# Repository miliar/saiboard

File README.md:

# Saiboard
Saiboard is an open-source Go board that combines tradition with technology.

Experience the thrill of Go on a real board, enhanced by AI guidance and analysis tools.

Play against AI, review your games with AI assistance, and elevate your Go skills to new heights.

https://github.com/miliar/saiboard/assets/35922697/eb32aec5-f142-464d-a071-56e9dbfe0f72

Features:

- Wooden Go [board](https://github.com/miliar/saiboard/tree/main/board) for authentic gameplay
- Sensory [electronics](https://github.com/miliar/saiboard/tree/main/electronics) for accurate move detection and LED feedback
- Heavy, magnetic Go [stones](https://github.com/miliar/saiboard/tree/main/stones) for a stable and engaging experience
- [Software](https://github.com/miliar/saiboard/tree/main/software ) with integrated AI system KataGo for expert insights and game recommendations
- User-friendly [web app](https://github.com/miliar/saiboard/tree/main/software/flutter/saiboard) for effortless control and interaction

## App

## Board
### Next moves

### Top moves

### Ownership

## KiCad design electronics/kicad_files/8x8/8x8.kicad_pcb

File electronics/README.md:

# Electronics
The electronics consists of one touch plate, an array of 19x19 hall sensors (for detecting magnets) and LEDs. \
The touch plate is used to detect when a move is finished, so that sliding the stone in position is possible. \
It is controlled by an ESP32S3 microcontroller.\
To make the manufacturing process easier, the board is divided into several smaller PCBs. \
There is a power connection for a raspberry pi.

## How to build
### PCBs

- [Order](https://jlcpcb.com/) PCB/ Stencil
- [Solderpaste](https://www.mouser.de/ProductDetail/Chip-Quik/TS391AX50?qs=1mbolxNpo8c66lK8U%252Bbg8g%3D%3D)
- Solder led side first
- [Reflow oven](https://www.ninjakitchen.de/produkte/ninja-foodi-8-in-1-multifunktionsofen-sp101eu-zidSP101EU?gclid=CjwKCAiAg6yRBhBNEiwAeVyL0K_J3ElNVxI_Z_oyhJKBGCfaiXaV0-DiEXvF-BnwtabYrZho8xsRyhoCo1UQAvD_BwE): Bake 3 min, 0-90s: 125° C, 90-180s: 230° C, then open door

- Print [plastic parts](/electronics/3d_prints/)
- Place pcb mask on first side, apply paste to the second side. Then remove pcb mask and bake pcb while placed on e.g. nuts

### Touch plate
Put copper foil on printed pcb-masks, remove foil from holes. Eletrical and physical connect all pcb masks. Glue non copper side to pcb first side with double sided tape. Solder connection to copper side and connect to touch pin of microcontroller.

### Mounting
- Press [esp32s3](https://docs.espressif.com/projects/esp-idf/en/latest/esp32s3/hw-reference/esp32s3/user-guide-devkitc-1.html#getting-started) in socket
- Use [screws](https://www.amazon.de/gp/product/B00XPJG1OC/ref=ppx_yo_dt_b_asin_title_o05_s00?ie=UTF8&psc=1) out of **stainless steel**.
- Enlarge mount holes of raspberry pi 4 to 3mm and fix it with the plastic mount. Connect power pins to board.
- Connect board power out to [adapter](https://www.amazon.de/Delock-Terminalblock-2pin-5mm-65421/dp/B009PH1J5Y/ref=pe_27091401_487027711_rtpb_2/259-0379054-1449235/ref=rtpb?_encoding=UTF8&pd_rd_i=B009PH1J5Y&pd_rd_w=x8W3O&content-id=amzn1.sym.474647f1-64c1-44ba-87f5-6213cf212586&pf_rd_p=474647f1-64c1-44ba-87f5-6213cf212586&pf_rd_r=0J4VFHEDP0EWMRD7EHXF&pd_rd_wg=oGq6l&pd_rd_r=6c2ec190-8354-4455-b1a1-8aa1fa129738&th=1). Glue adapter into hole on the side of the board.
- Use a 5V/ 10A, 50W [power supply](https://www.amazon.de/LEICKE-Netzteil-Adapter-WS2812B-LED8806/dp/B07YVBHH6K?pd_rd_w=0m35S&content-id=amzn1.sym.5a3fbeeb-1af1-4617-a0f9-8268dbe71de3&pf_rd_p=5a3fbeeb-1af1-4617-a0f9-8268dbe71de3&pf_rd_r=37PZ5YX5WHR4K52V4X9C&pd_rd_wg=4ZrhK&pd_rd_r=1ae78b2e-2f51-4e24-866a-adc47f1cd7c7&pd_rd_i=B07YVBHH6K&psc=1&ref_=pd_basp_d_rpt_ba_s_3_t)

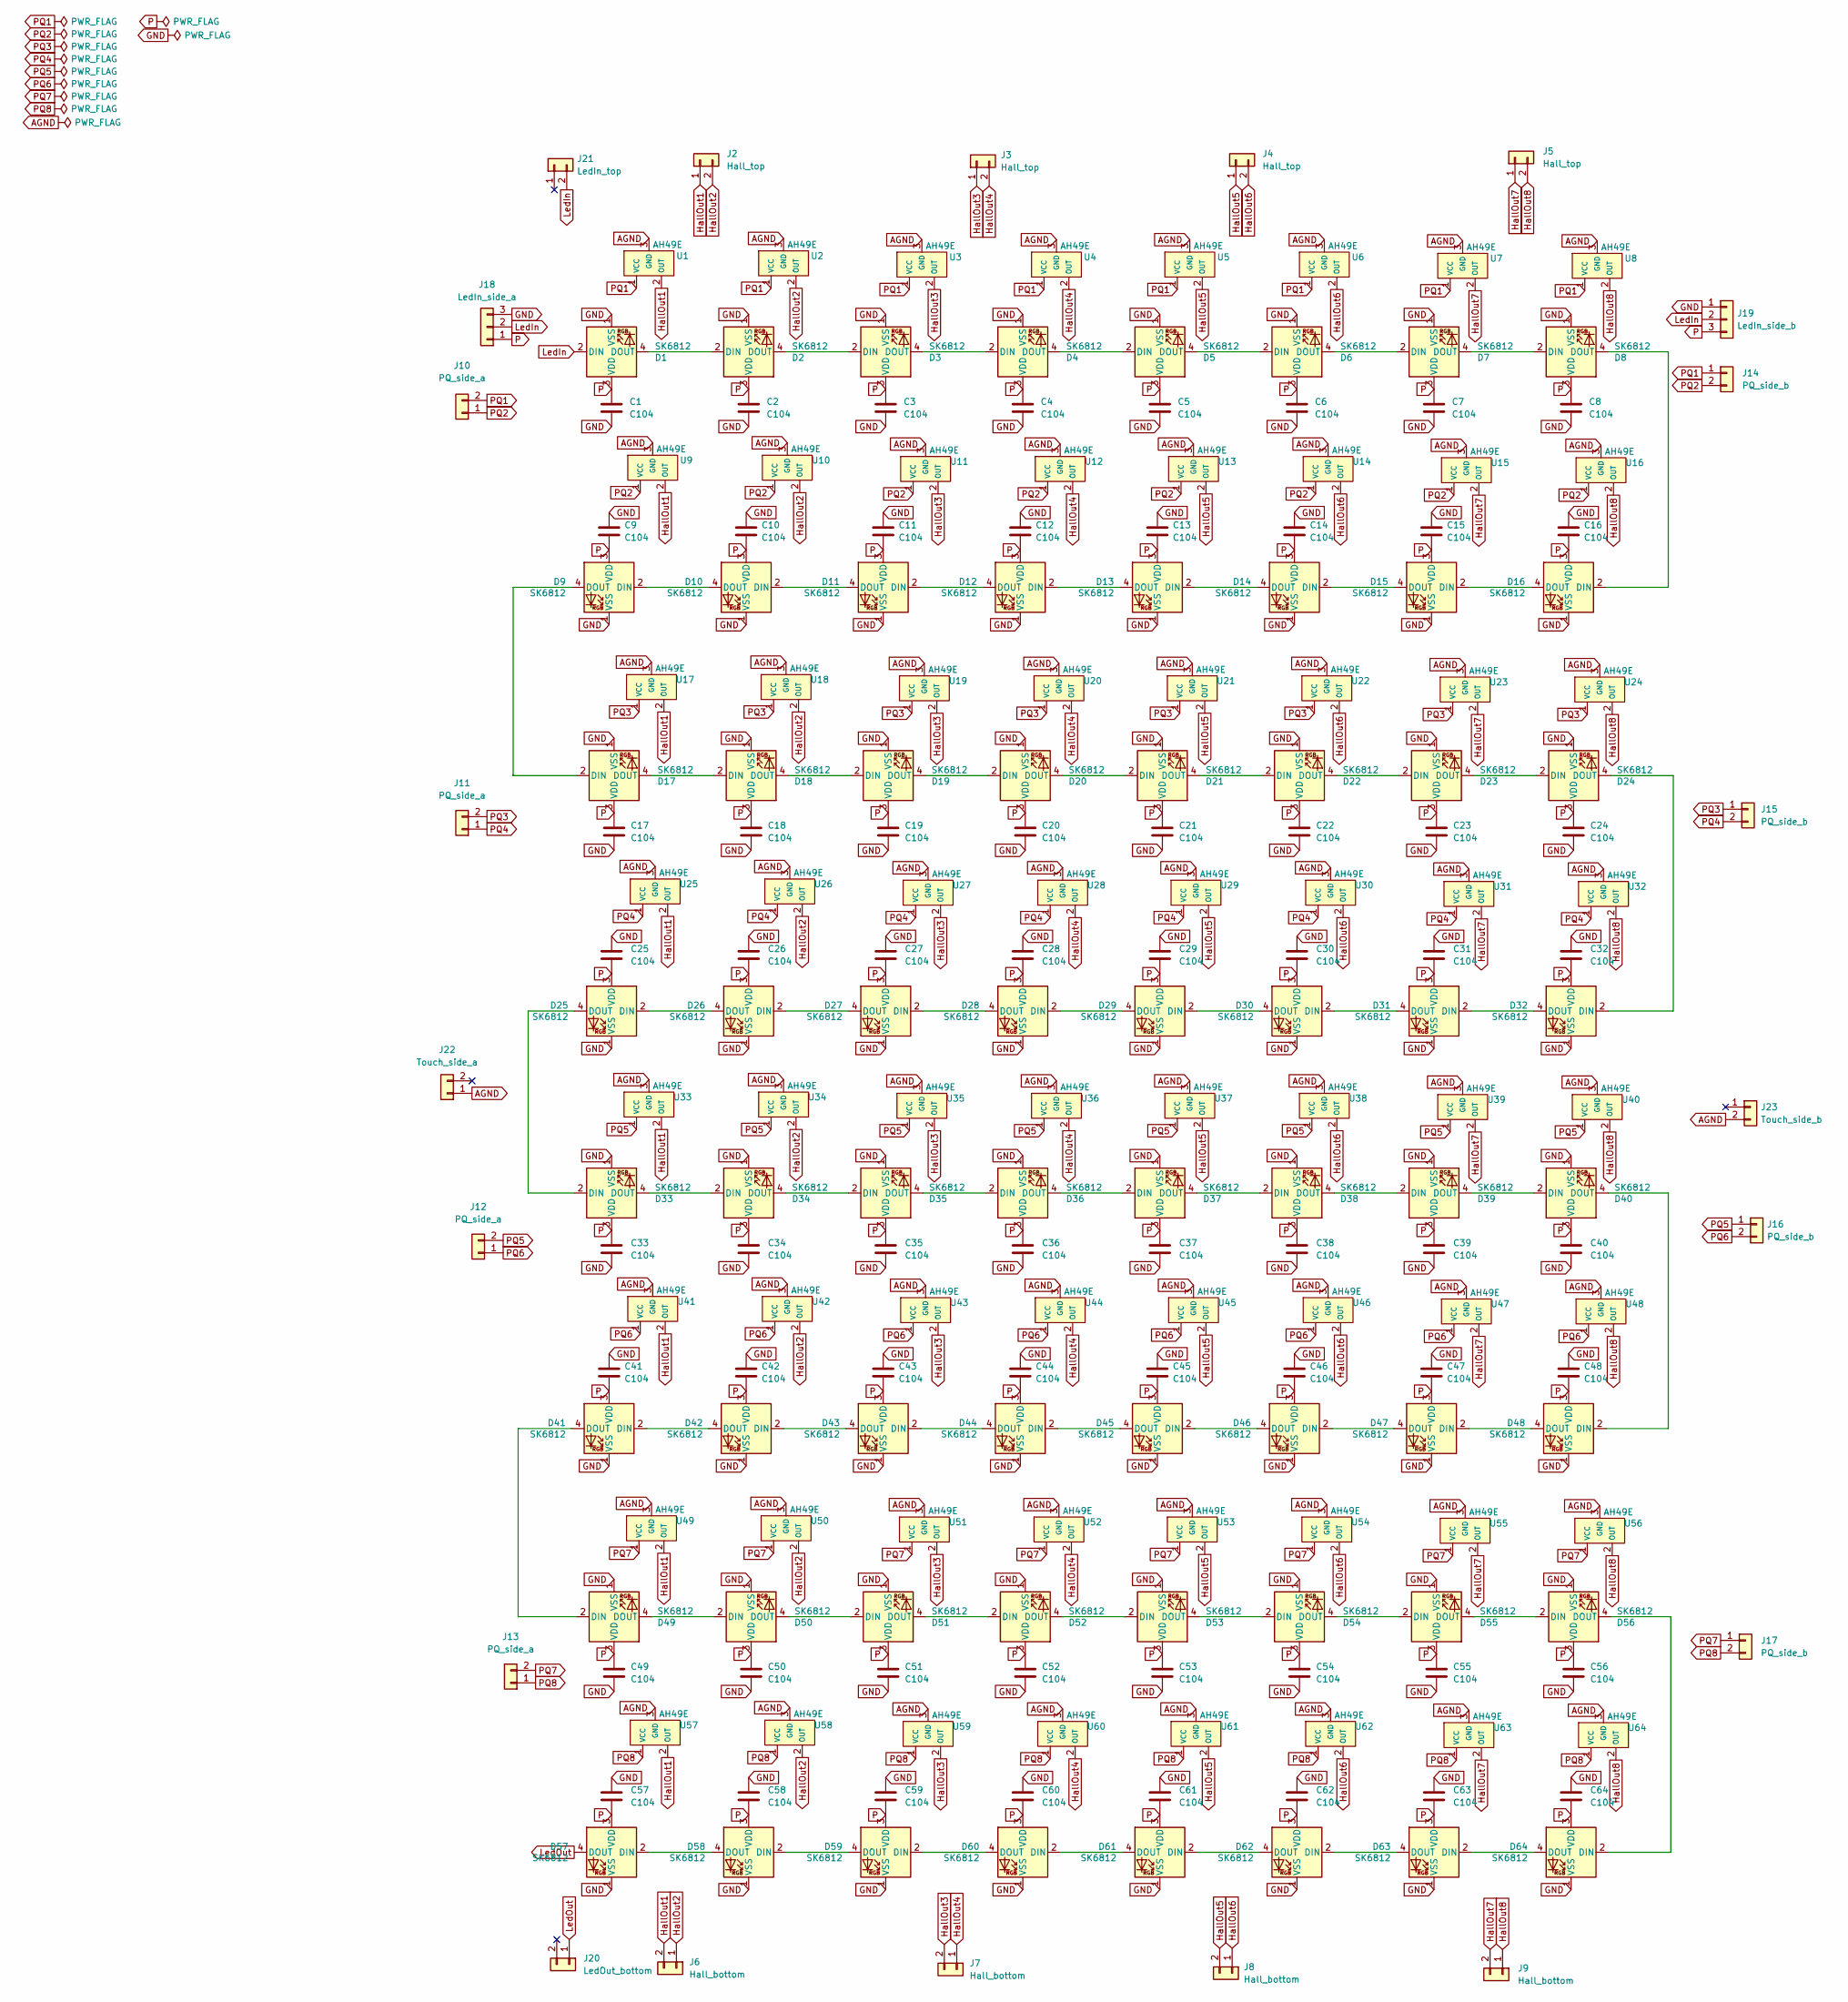
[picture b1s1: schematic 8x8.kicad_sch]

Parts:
C1, C2, C3, C4, C5, C6, C7, C8, C9, C10, C11, C12, C13, C14, C15, C16, C17, C18, C19, C20, C21, C22, C23, C24, C25, C26, C27, C28, C29, C30, C31, C32, C33, C34, C35, C36, C37, C38, C39, C40, C41, C42, C43, C44, C45, C46, C47, C48, C49, C50, C51, C52, C53, C54, C55, C56, C57, C58, C59, C60, C61, C62, C63, C64: C104; C_1206_3216Metric
D1, D2, D3, D4, D5, D6, D7, D8, D9, D10, D11, D12, D13, D14, D15, D16, D17, D18, D19, D20, D21, D22, D23, D24, D25, D26, D27, D28, D29, D30, D31, D32, D33, D34, D35, D36, D37, D38, D39, D40, D41, D42, D43, D44, D45, D46, D47, D48, D49, D50, D51, D52, D53, D54, D55, D56, D57, D58, D59, D60, D61, D62, D63, D64: SK6812; LED_SK6812_PLCC4_5.0x5.0mm_P3.2mm
J2, J3, J4, J5: Hall_top; PinHeader_1x02_P2.54mm_Horizontal_SMD
J6, J7, J8, J9: Hall_bottom; PinSocket_1x02_P2.54mm_Horizontal_SMD
J10, J11, J12, J13: PQ_side_a; PinSocket_1x02_P2.54mm_Horizontal_SMD
J14, J15, J16, J17: PQ_side_b; PinSocket_1x02_P2.54mm_Horizontal_SMD
J18: LedIn_side_a; PinSocket_1x03_P2.54mm_Horizontal_SMD
J19: LedIn_side_b; PinSocket_1x03_P2.54mm_Horizontal_SMD
J20: LedOut_bottom; PinSocket_1x02_P2.54mm_Horizontal_SMD
J21: LedIn_top; PinHeader_1x02_P2.54mm_Horizontal_SMD
J22: Touch_side_a; PinSocket_1x02_P2.54mm_Horizontal_SMD
J23: Touch_side_b; PinSocket_1x02_P2.54mm_Horizontal_SMD
U1, U2, U3, U4, U5, U6, U7, U8, U9, U10, U11, U12, U13, U14, U15, U16, U17, U18, U19, U20, U21, U22, U23, U24, U25, U26, U27, U28, U29, U30, U31, U32, U33, U34, U35, U36, U37, U38, U39, U40, U41, U42, U43, U44, U45, U46, U47, U48, U49, U50, U51, U52, U53, U54, U55, U56, U57, U58, U59, U60, U61, U62, U63, U64: AH49E; SOT-23

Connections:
AGND: J22.1, J23.2, U1.3 (GND), U2.3 (GND), U3.3 (GND), U4.3 (GND), U5.3 (GND), U6.3 (GND), U7.3 (GND), U8.3 (GND), U9.3 (GND), U10.3 (GND), U11.3 (GND), U12.3 (GND), U13.3 (GND), U14.3 (GND), U15.3 (GND), U16.3 (GND), U17.3 (GND), U18.3 (GND), U19.3 (GND), U20.3 (GND), U21.3 (GND), U22.3 (GND), U23.3 (GND), U24.3 (GND), U25.3 (GND), U26.3 (GND), U27.3 (GND), U28.3 (GND), U29.3 (GND), U30.3 (GND), U31.3 (GND), U32.3 (GND), U33.3 (GND), U34.3 (GND), U35.3 (GND), U36.3 (GND), U37.3 (GND), U38.3 (GND), U39.3 (GND), U40.3 (GND), U41.3 (GND), U42.3 (GND), U43.3 (GND), U44.3 (GND), U45.3 (GND), U46.3 (GND), U47.3 (GND), U48.3 (GND), U49.3 (GND), U50.3 (GND), U51.3 (GND), U52.3 (GND), U53.3 (GND), U54.3 (GND), U55.3 (GND), U56.3 (GND), U57.3 (GND), U58.3 (GND), U59.3 (GND), U60.3 (GND), U61.3 (GND), U62.3 (GND), U63.3 (GND), U64.3 (GND)
GND: C1.2, C2.2, C3.2, C4.2, C5.2, C6.2, C7.2, C8.2, C9.2, C10.2, C11.2, C12.2, C13.2, C14.2, C15.2, C16.2, C17.2, C18.2, C19.2, C20.2, C21.2, C22.2, C23.2, C24.2, C25.2, C26.2, C27.2, C28.2, C29.2, C30.2, C31.2, C32.2, C33.2, C34.2, C35.2, C36.2, C37.2, C38.2, C39.2, C40.2, C41.2, C42.2, C43.2, C44.2, C45.2, C46.2, C47.2, C48.2, C49.2, C50.2, C51.2, C52.2, C53.2, C54.2, C55.2, C56.2, C57.2, C58.2, C59.2, C60.2, C61.2, C62.2, C63.2, C64.2, D1.1 (VSS), D2.1 (VSS), D3.1 (VSS), D4.1 (VSS), D5.1 (VSS), D6.1 (VSS), D7.1 (VSS), D8.1 (VSS), D9.1 (VSS), D10.1 (VSS), D11.1 (VSS), D12.1 (VSS), D13.1 (VSS), D14.1 (VSS), D15.1 (VSS), D16.1 (VSS), D17.1 (VSS), D18.1 (VSS), D19.1 (VSS), D20.1 (VSS), D21.1 (VSS), D22.1 (VSS), D23.1 (VSS), D24.1 (VSS), D25.1 (VSS), D26.1 (VSS), D27.1 (VSS), D28.1 (VSS), D29.1 (VSS), D30.1 (VSS), D31.1 (VSS), D32.1 (VSS), D33.1 (VSS), D34.1 (VSS), D35.1 (VSS), D36.1 (VSS), D37.1 (VSS), D38.1 (VSS), D39.1 (VSS), D40.1 (VSS), D41.1 (VSS), D42.1 (VSS), D43.1 (VSS), D44.1 (VSS), D45.1 (VSS), D46.1 (VSS), D47.1 (VSS), D48.1 (VSS), D49.1 (VSS), D50.1 (VSS), D51.1 (VSS), D52.1 (VSS), D53.1 (VSS), D54.1 (VSS), D55.1 (VSS), D56.1 (VSS), D57.1 (VSS), D58.1 (VSS), D59.1 (VSS), D60.1 (VSS), D61.1 (VSS), D62.1 (VSS), D63.1 (VSS), D64.1 (VSS), J18.3, J19.1
HallOut1: J2.1, J6.2, U1.2 (OUT), U9.2 (OUT), U17.2 (OUT), U25.2 (OUT), U33.2 (OUT), U41.2 (OUT), U49.2 (OUT), U57.2 (OUT)
HallOut2: J2.2, J6.1, U2.2 (OUT), U10.2 (OUT), U18.2 (OUT), U26.2 (OUT), U34.2 (OUT), U42.2 (OUT), U50.2 (OUT), U58.2 (OUT)
HallOut3: J3.1, J7.2, U3.2 (OUT), U11.2 (OUT), U19.2 (OUT), U27.2 (OUT), U35.2 (OUT), U43.2 (OUT), U51.2 (OUT), U59.2 (OUT)
HallOut4: J3.2, J7.1, U4.2 (OUT), U12.2 (OUT), U20.2 (OUT), U28.2 (OUT), U36.2 (OUT), U44.2 (OUT), U52.2 (OUT), U60.2 (OUT)
HallOut5: J4.1, J8.2, U5.2 (OUT), U13.2 (OUT), U21.2 (OUT), U29.2 (OUT), U37.2 (OUT), U45.2 (OUT), U53.2 (OUT), U61.2 (OUT)
HallOut6: J4.2, J8.1, U6.2 (OUT), U14.2 (OUT), U22.2 (OUT), U30.2 (OUT), U38.2 (OUT), U46.2 (OUT), U54.2 (OUT), U62.2 (OUT)
HallOut7: J5.1, J9.2, U7.2 (OUT), U15.2 (OUT), U23.2 (OUT), U31.2 (OUT), U39.2 (OUT), U47.2 (OUT), U55.2 (OUT), U63.2 (OUT)
HallOut8: J5.2, J9.1, U8.2 (OUT), U16.2 (OUT), U24.2 (OUT), U32.2 (OUT), U40.2 (OUT), U48.2 (OUT), U56.2 (OUT), U64.2 (OUT)
LedIn: D1.2 (DIN), J18.2, J19.2, J21.2
LedOut: D57.4 (DOUT), J20.1
unnamed: D1.4 (DOUT), D2.2 (DIN)
unnamed: D2.4 (DOUT), D3.2 (DIN)
unnamed: D3.4 (DOUT), D4.2 (DIN)
unnamed: D4.4 (DOUT), D5.2 (DIN)
unnamed: D5.4 (DOUT), D6.2 (DIN)
unnamed: D6.4 (DOUT), D7.2 (DIN)
unnamed: D7.4 (DOUT), D8.2 (DIN)
unnamed: D10.2 (DIN), D11.4 (DOUT)
unnamed: D9.2 (DIN), D10.4 (DOUT)
unnamed: D11.2 (DIN), D12.4 (DOUT)
unnamed: D12.2 (DIN), D13.4 (DOUT)
unnamed: D13.2 (DIN), D14.4 (DOUT)
unnamed: D14.2 (DIN), D15.4 (DOUT)
unnamed: D15.2 (DIN), D16.4 (DOUT)
unnamed: D8.4 (DOUT), D16.2 (DIN)
unnamed: D9.4 (DOUT), D17.2 (DIN)
unnamed: D17.4 (DOUT), D18.2 (DIN)
unnamed: D18.4 (DOUT), D19.2 (DIN)
unnamed: D19.4 (DOUT), D20.2 (DIN)
unnamed: D20.4 (DOUT), D21.2 (DIN)
unnamed: D21.4 (DOUT), D22.2 (DIN)
unnamed: D22.4 (DOUT), D23.2 (DIN)
unnamed: D23.4 (DOUT), D24.2 (DIN)
unnamed: D24.4 (DOUT), D32.2 (DIN)
unnamed: D25.2 (DIN), D26.4 (DOUT)
unnamed: D25.4 (DOUT), D33.2 (DIN)
unnamed: D26.2 (DIN), D27.4 (DOUT)
unnamed: D27.2 (DIN), D28.4 (DOUT)
unnamed: D28.2 (DIN), D29.4 (DOUT)
unnamed: D29.2 (DIN), D30.4 (DOUT)
unnamed: D30.2 (DIN), D31.4 (DOUT)
unnamed: D31.2 (DIN), D32.4 (DOUT)
unnamed: D33.4 (DOUT), D34.2 (DIN)
unnamed: D34.4 (DOUT), D35.2 (DIN)
unnamed: D35.4 (DOUT), D36.2 (DIN)
unnamed: D36.4 (DOUT), D37.2 (DIN)
unnamed: D37.4 (DOUT), D38.2 (DIN)
unnamed: D38.4 (DOUT), D39.2 (DIN)
unnamed: D39.4 (DOUT), D40.2 (DIN)
unnamed: D40.4 (DOUT), D48.2 (DIN)
unnamed: D41.2 (DIN), D42.4 (DOUT)
unnamed: D41.4 (DOUT), D49.2 (DIN)
unnamed: D42.2 (DIN), D43.4 (DOUT)
unnamed: D43.2 (DIN), D44.4 (DOUT)
unnamed: D44.2 (DIN), D45.4 (DOUT)
unnamed: D45.2 (DIN), D46.4 (DOUT)
unnamed: D46.2 (DIN), D47.4 (DOUT)
unnamed: D47.2 (DIN), D48.4 (DOUT)
unnamed: D49.4 (DOUT), D50.2 (DIN)
unnamed: D50.4 (DOUT), D51.2 (DIN)
unnamed: D51.4 (DOUT), D52.2 (DIN)
unnamed: D52.4 (DOUT), D53.2 (DIN)
unnamed: D53.4 (DOUT), D54.2 (DIN)
unnamed: D54.4 (DOUT), D55.2 (DIN)
unnamed: D55.4 (DOUT), D56.2 (DIN)
unnamed: D56.4 (DOUT), D64.2 (DIN)
unnamed: D57.2 (DIN), D58.4 (DOUT)
unnamed: D58.2 (DIN), D59.4 (DOUT)
unnamed: D59.2 (DIN), D60.4 (DOUT)
unnamed: D60.2 (DIN), D61.4 (DOUT)
unnamed: D61.2 (DIN), D62.4 (DOUT)
unnamed: D62.2 (DIN), D63.4 (DOUT)
unnamed: D63.2 (DIN), D64.4 (DOUT)
P: C1.1, C2.1, C3.1, C4.1, C5.1, C6.1, C7.1, C8.1, C9.1, C10.1, C11.1, C12.1, C13.1, C14.1, C15.1, C16.1, C17.1, C18.1, C19.1, C20.1, C21.1, C22.1, C23.1, C24.1, C25.1, C26.1, C27.1, C28.1, C29.1, C30.1, C31.1, C32.1, C33.1, C34.1, C35.1, C36.1, C37.1, C38.1, C39.1, C40.1, C41.1, C42.1, C43.1, C44.1, C45.1, C46.1, C47.1, C48.1, C49.1, C50.1, C51.1, C52.1, C53.1, C54.1, C55.1, C56.1, C57.1, C58.1, C59.1, C60.1, C61.1, C62.1, C63.1, C64.1, D1.3 (VDD), D2.3 (VDD), D3.3 (VDD), D4.3 (VDD), D5.3 (VDD), D6.3 (VDD), D7.3 (VDD), D8.3 (VDD), D9.3 (VDD), D10.3 (VDD), D11.3 (VDD), D12.3 (VDD), D13.3 (VDD), D14.3 (VDD), D15.3 (VDD), D16.3 (VDD), D17.3 (VDD), D18.3 (VDD), D19.3 (VDD), D20.3 (VDD), D21.3 (VDD), D22.3 (VDD), D23.3 (VDD), D24.3 (VDD), D25.3 (VDD), D26.3 (VDD), D27.3 (VDD), D28.3 (VDD), D29.3 (VDD), D30.3 (VDD), D31.3 (VDD), D32.3 (VDD), D33.3 (VDD), D34.3 (VDD), D35.3 (VDD), D36.3 (VDD), D37.3 (VDD), D38.3 (VDD), D39.3 (VDD), D40.3 (VDD), D41.3 (VDD), D42.3 (VDD), D43.3 (VDD), D44.3 (VDD), D45.3 (VDD), D46.3 (VDD), D47.3 (VDD), D48.3 (VDD), D49.3 (VDD), D50.3 (VDD), D51.3 (VDD), D52.3 (VDD), D53.3 (VDD), D54.3 (VDD), D55.3 (VDD), D56.3 (VDD), D57.3 (VDD), D58.3 (VDD), D59.3 (VDD), D60.3 (VDD), D61.3 (VDD), D62.3 (VDD), D63.3 (VDD), D64.3 (VDD), J18.1, J19.3
PQ1: J10.2, J14.1, U1.1 (VCC), U2.1 (VCC), U3.1 (VCC), U4.1 (VCC), U5.1 (VCC), U6.1 (VCC), U7.1 (VCC), U8.1 (VCC)
PQ2: J10.1, J14.2, U9.1 (VCC), U10.1 (VCC), U11.1 (VCC), U12.1 (VCC), U13.1 (VCC), U14.1 (VCC), U15.1 (VCC), U16.1 (VCC)
PQ3: J11.2, J15.1, U17.1 (VCC), U18.1 (VCC), U19.1 (VCC), U20.1 (VCC), U21.1 (VCC), U22.1 (VCC), U23.1 (VCC), U24.1 (VCC)
PQ4: J11.1, J15.2, U25.1 (VCC), U26.1 (VCC), U27.1 (VCC), U28.1 (VCC), U29.1 (VCC), U30.1 (VCC), U31.1 (VCC), U32.1 (VCC)
PQ5: J12.2, J16.1, U33.1 (VCC), U34.1 (VCC), U35.1 (VCC), U36.1 (VCC), U37.1 (VCC), U38.1 (VCC), U39.1 (VCC), U40.1 (VCC)
PQ6: J12.1, J16.2, U41.1 (VCC), U42.1 (VCC), U43.1 (VCC), U44.1 (VCC), U45.1 (VCC), U46.1 (VCC), U47.1 (VCC), U48.1 (VCC)
PQ7: J13.2, J17.1, U49.1 (VCC), U50.1 (VCC), U51.1 (VCC), U52.1 (VCC), U53.1 (VCC), U54.1 (VCC), U55.1 (VCC), U56.1 (VCC)
PQ8: J13.1, J17.2, U57.1 (VCC), U58.1 (VCC), U59.1 (VCC), U60.1 (VCC), U61.1 (VCC), U62.1 (VCC), U63.1 (VCC), U64.1 (VCC)

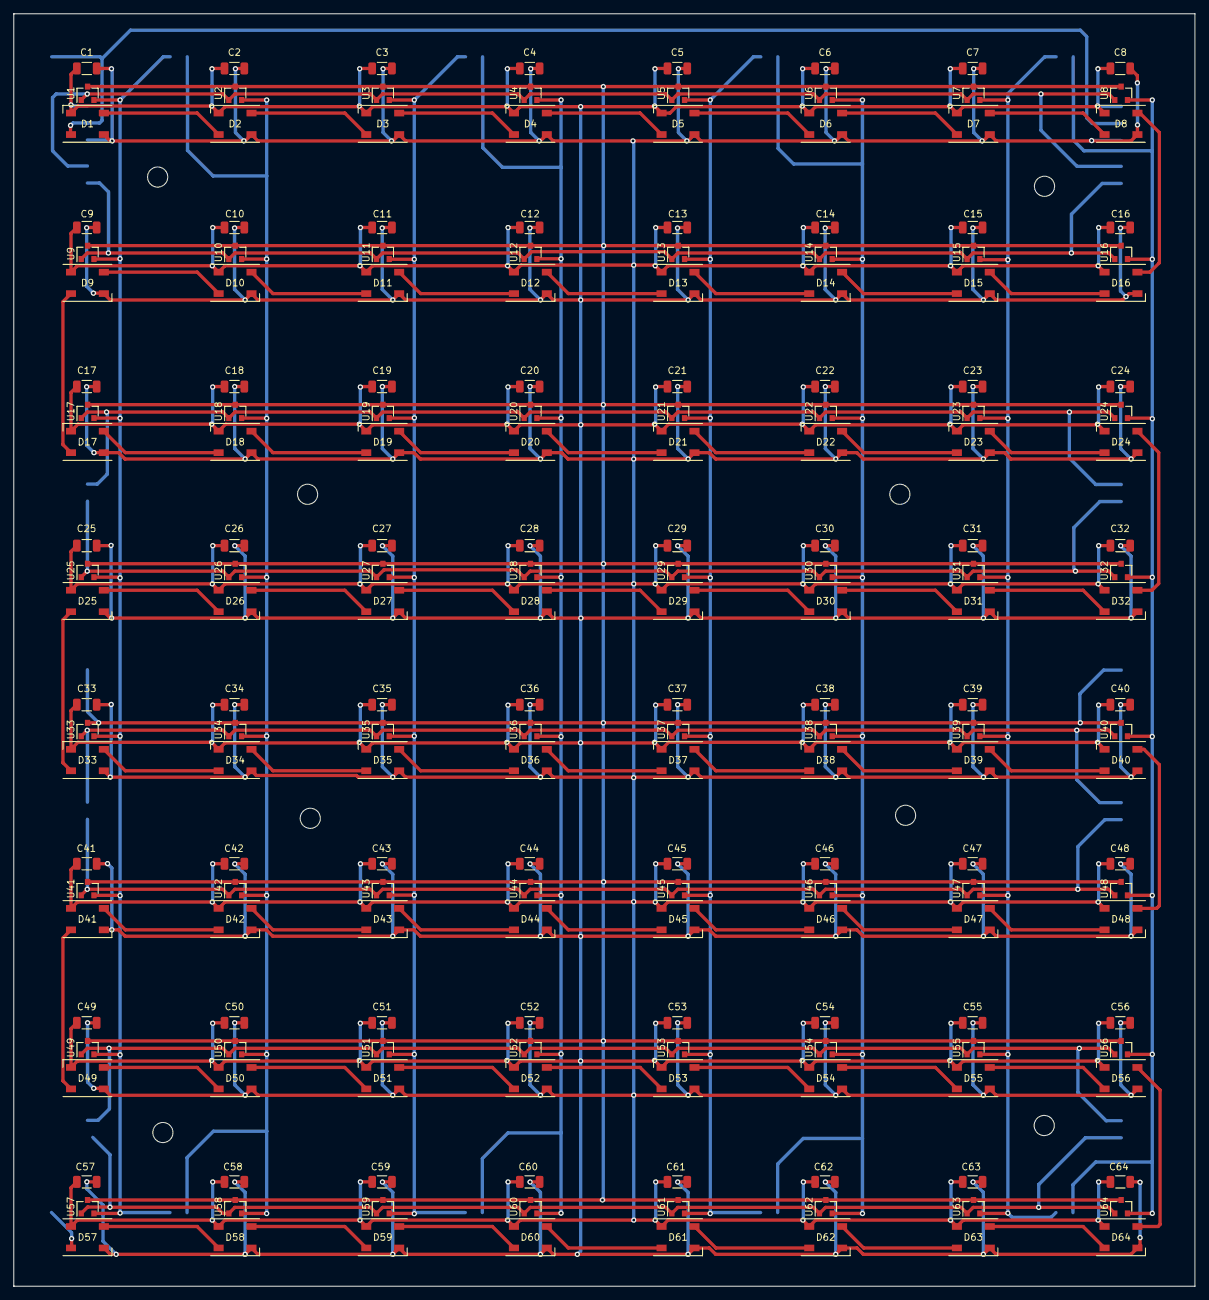
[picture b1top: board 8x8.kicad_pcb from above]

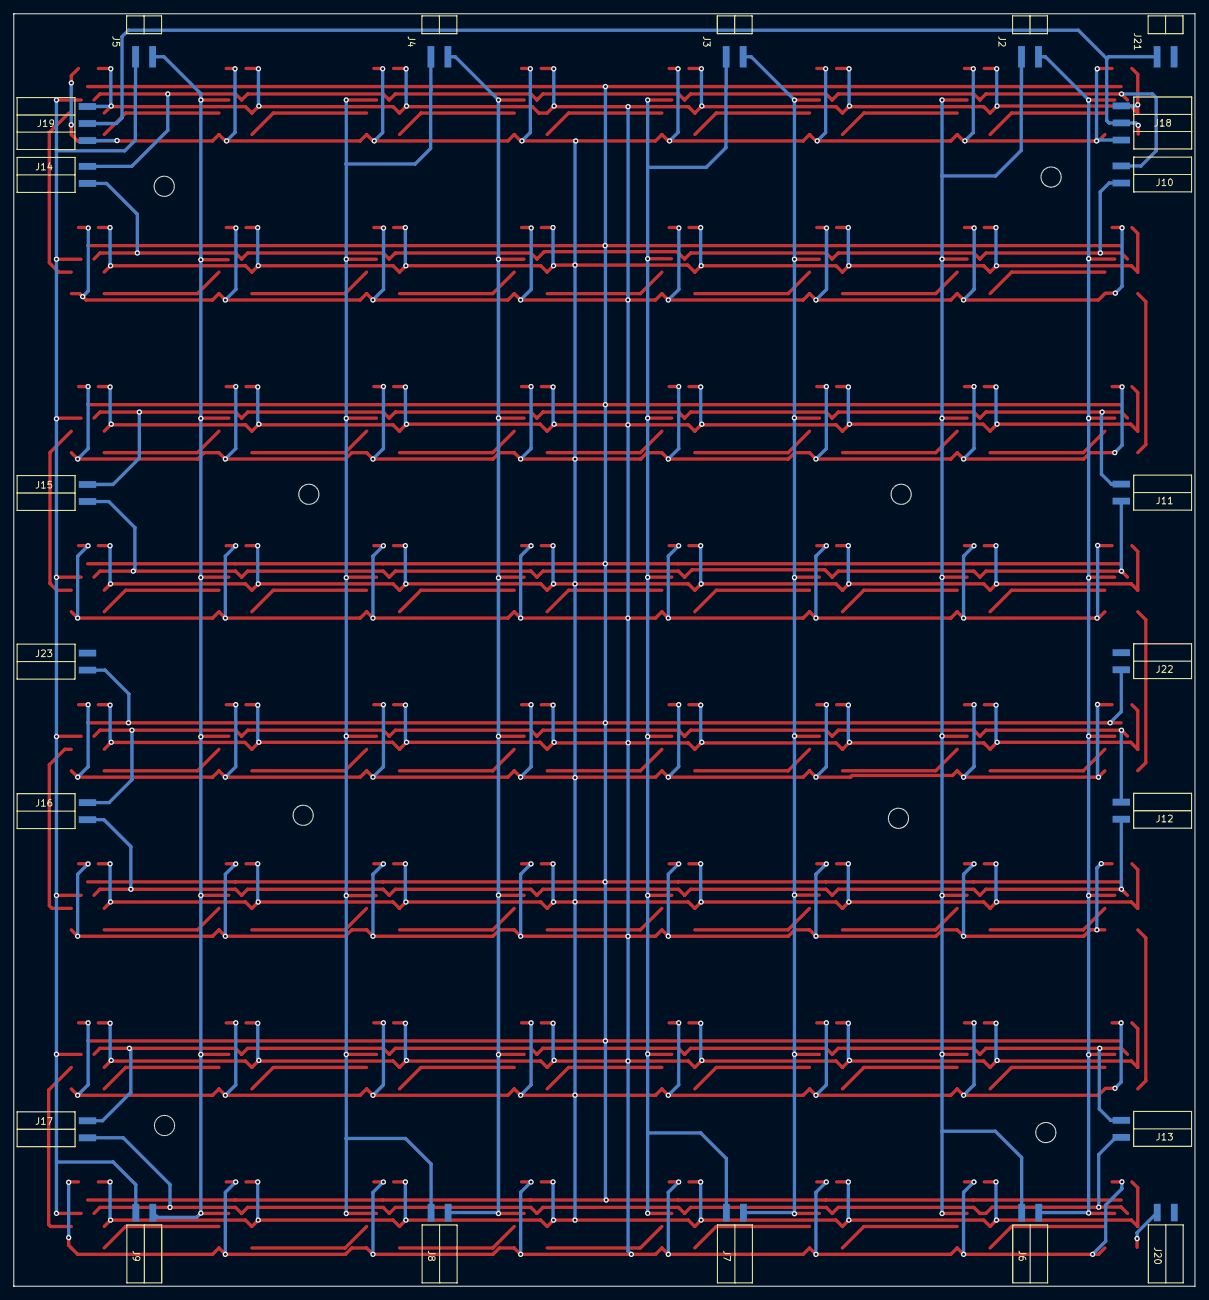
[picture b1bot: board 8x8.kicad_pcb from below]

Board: 2 copper layers, 176.0 x 189.6 mm, 222 parts (22 on the bottom side), 84 nets.

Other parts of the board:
m1, m1#2, m1#3, m1#4, m1#5, m1#6, m1#7, m2: MountingHole_3mm

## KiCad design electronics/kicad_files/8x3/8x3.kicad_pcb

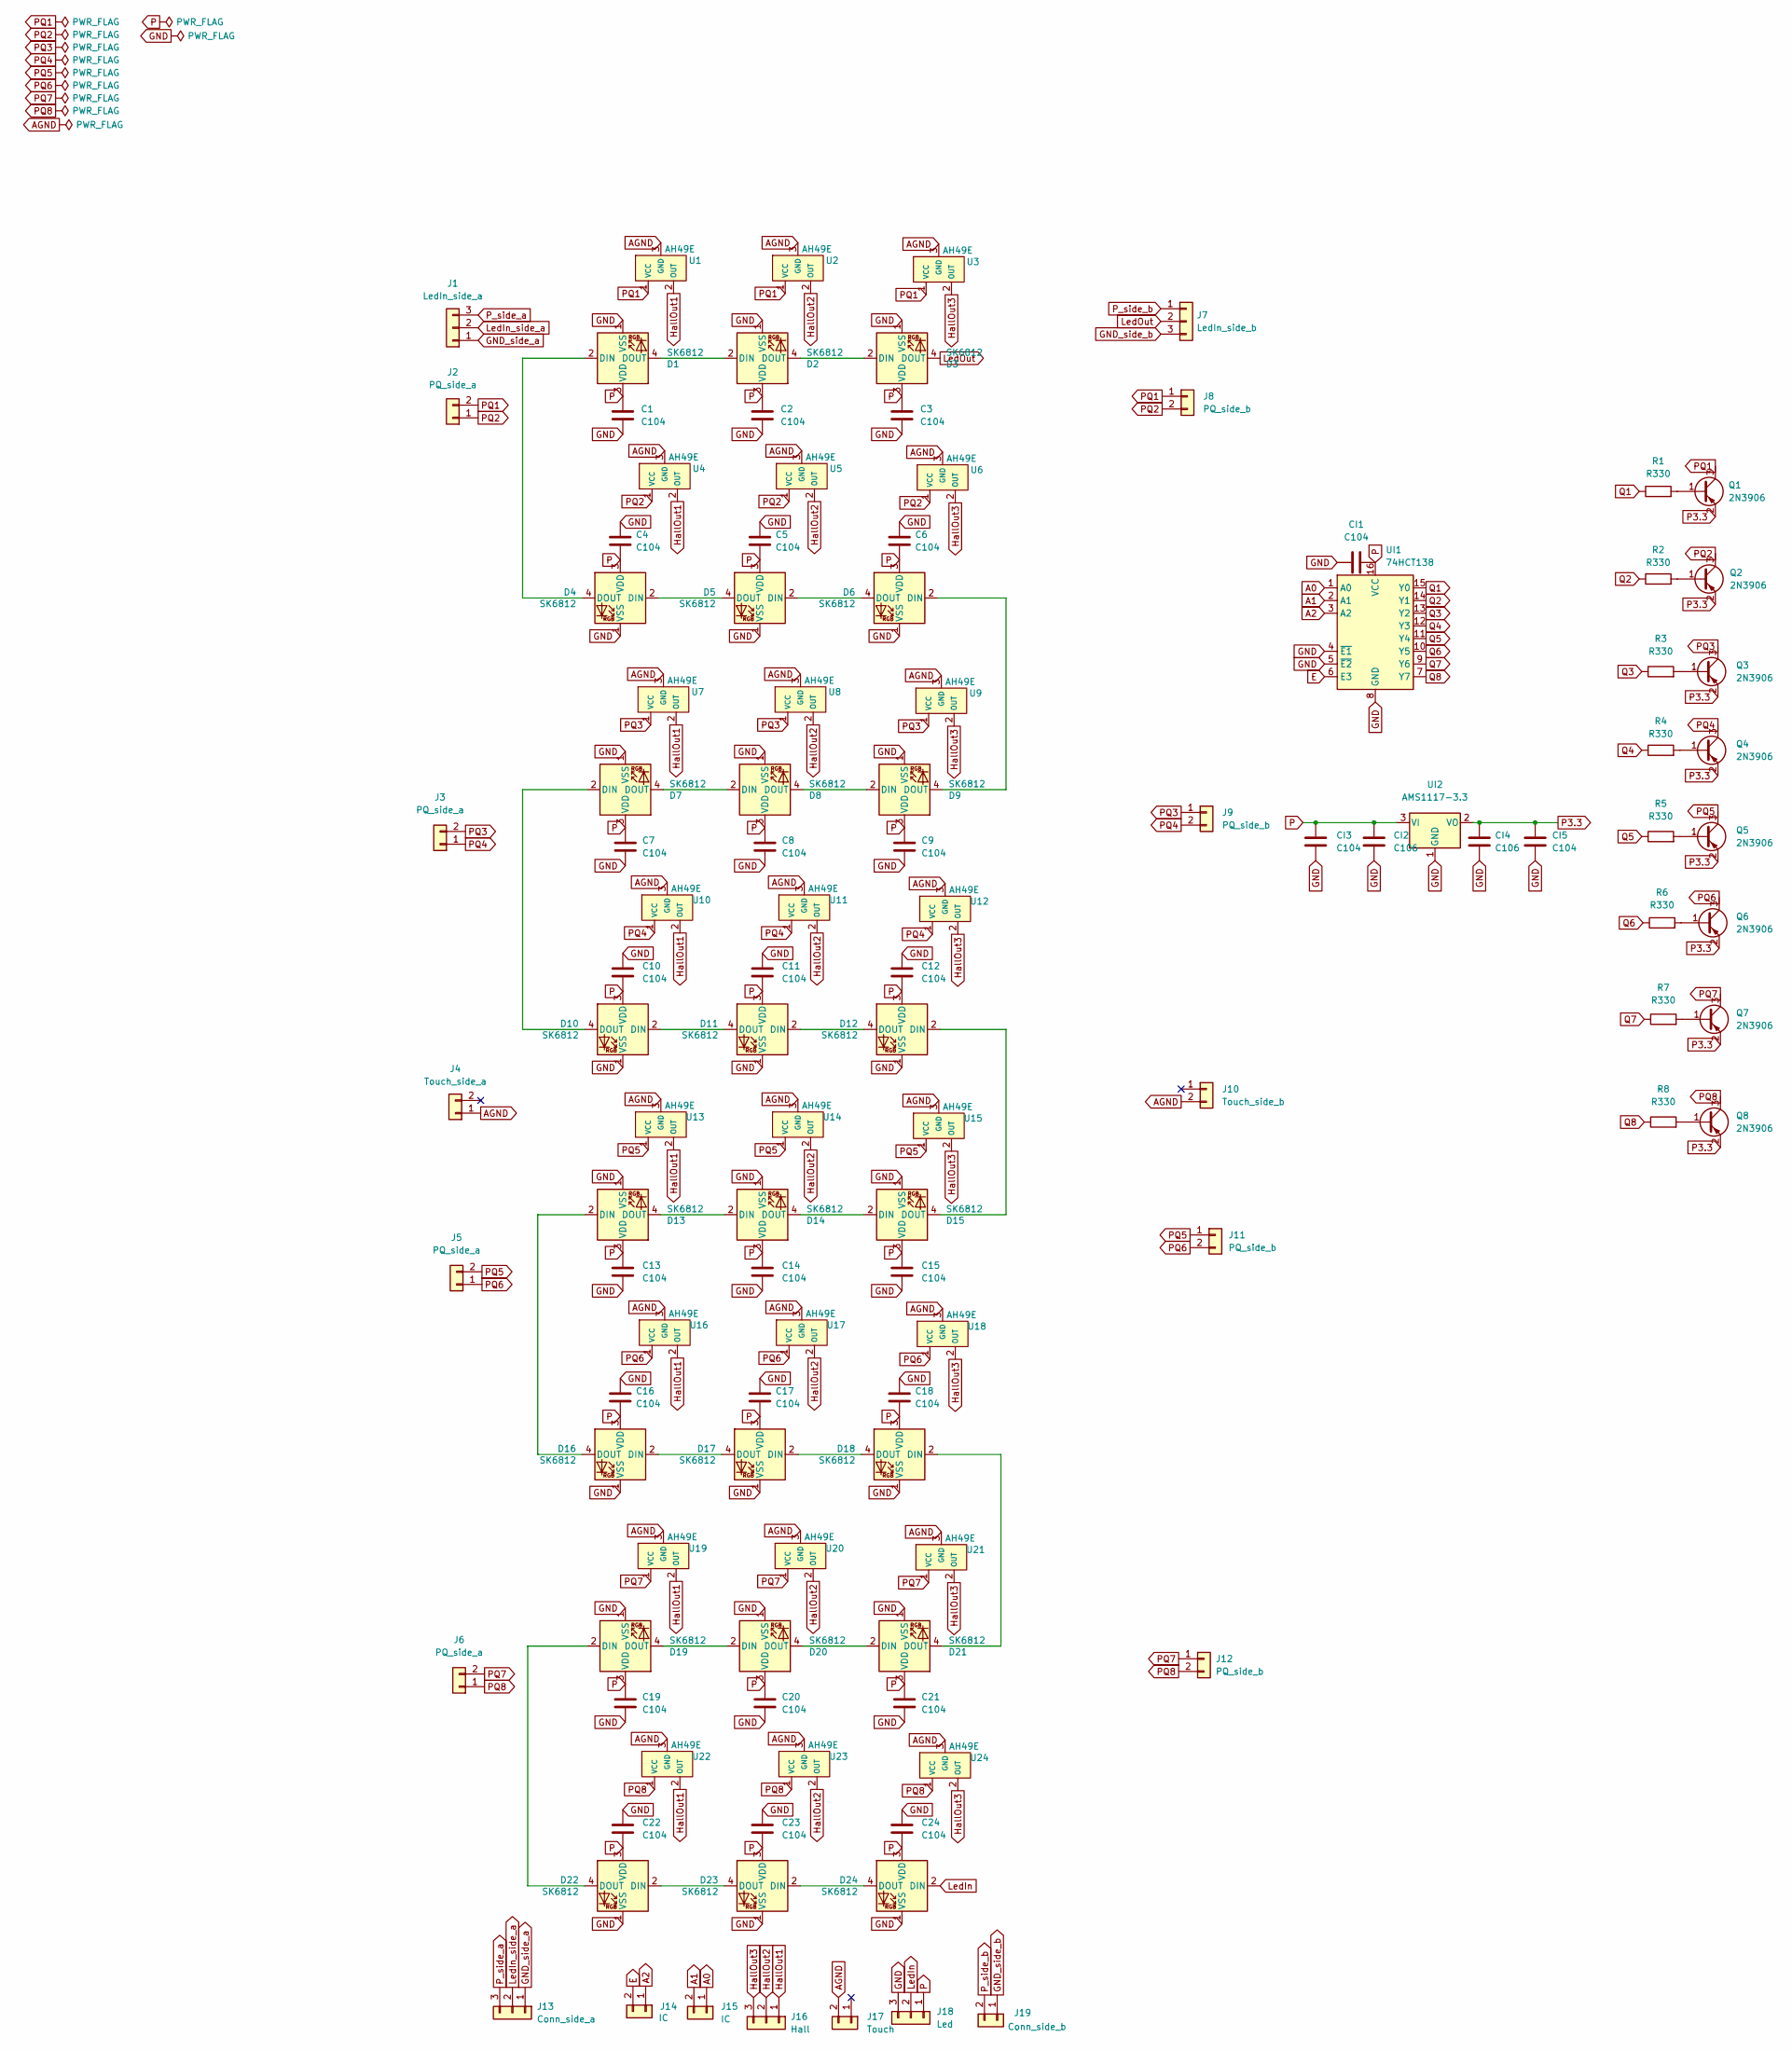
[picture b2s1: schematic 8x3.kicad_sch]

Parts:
C1, C2, C3, C4, C5, C6, C7, C8, C9, C10, C11, C12, C13, C14, C15, C16, C17, C18, C19, C20, C21, C22, C23, C24: C104; C_1206_3216Metric
CI1, CI3, CI5: C104; C_1206_3216Metric
CI2, CI4: C106; C_1206_3216Metric
D1, D2, D3, D4, D5, D6, D7, D8, D9, D10, D11, D12, D13, D14, D15, D16, D17, D18, D19, D20, D21, D22, D23, D24: SK6812; LED_SK6812_PLCC4_5.0x5.0mm_P3.2mm
J1: LedIn_side_a; PinHeader_1x03_P2.54mm_Horizontal_SMD
J2, J3, J5, J6: PQ_side_a; PinHeader_1x02_P2.54mm_Horizontal_SMD
J4: Touch_side_a; PinHeader_1x02_P2.54mm_Horizontal_SMD
J7: LedIn_side_b; PinHeader_1x03_P2.54mm_Horizontal_SMD
J8, J9, J11, J12: PQ_side_b; PinHeader_1x02_P2.54mm_Horizontal_SMD
J10: Touch_side_b; PinHeader_1x02_P2.54mm_Horizontal_SMD
J13: Conn_side_a; PinHeader_1x03_P2.54mm_Horizontal_SMD
J14, J15: IC; PinHeader_1x02_P2.54mm_Horizontal_SMD
J16: Hall; PinHeader_1x03_P2.54mm_Horizontal_SMD
J17: Touch; PinHeader_1x02_P2.54mm_Horizontal_SMD
J18: Led; PinHeader_1x03_P2.54mm_Horizontal_SMD
J19: Conn_side_b; PinHeader_1x02_P2.54mm_Horizontal_SMD
Q1, Q2, Q3, Q4, Q5, Q6, Q7, Q8: 2N3906; SOT-23
R1, R2, R3, R4, R5, R6, R7, R8: R330; R_1206_3216Metric
U1, U2, U3, U4, U5, U6, U7, U8, U9, U10, U11, U12, U13, U14, U15, U16, U17, U18, U19, U20, U21, U22, U23, U24: AH49E; SOT-23
UI1: 74HCT138; SO-16_5.3x10.2mm_P1.27mm
UI2: AMS1117-3.3; SOT-223

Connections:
A0: J15.1, UI1.1 (A0)
A1: J15.2, UI1.2 (A1)
A2: J14.1, UI1.3 (A2)
AGND: J4.1, J10.2, J17.2, U1.3 (GND), U2.3 (GND), U3.3 (GND), U4.3 (GND), U5.3 (GND), U6.3 (GND), U7.3 (GND), U8.3 (GND), U9.3 (GND), U10.3 (GND), U11.3 (GND), U12.3 (GND), U13.3 (GND), U14.3 (GND), U15.3 (GND), U16.3 (GND), U17.3 (GND), U18.3 (GND), U19.3 (GND), U20.3 (GND), U21.3 (GND), U22.3 (GND), U23.3 (GND), U24.3 (GND)
E: J14.2, UI1.6 (E3)
GND: C1.2, C2.2, C3.2, C4.2, C5.2, C6.2, C7.2, C8.2, C9.2, C10.2, C11.2, C12.2, C13.2, C14.2, C15.2, C16.2, C17.2, C18.2, C19.2, C20.2, C21.2, C22.2, C23.2, C24.2, CI1.1, CI2.1, CI3.1, CI4.1, CI5.1, D1.1 (VSS), D2.1 (VSS), D3.1 (VSS), D4.1 (VSS), D5.1 (VSS), D6.1 (VSS), D7.1 (VSS), D8.1 (VSS), D9.1 (VSS), D10.1 (VSS), D11.1 (VSS), D12.1 (VSS), D13.1 (VSS), D14.1 (VSS), D15.1 (VSS), D16.1 (VSS), D17.1 (VSS), D18.1 (VSS), D19.1 (VSS), D20.1 (VSS), D21.1 (VSS), D22.1 (VSS), D23.1 (VSS), D24.1 (VSS), J18.3, UI1.4 (~E1), UI1.5 (~E2), UI1.8 (GND), UI2.1 (GND)
GND_side_a: J1.1, J13.1
GND_side_b: J7.3, J19.1
HallOut1: J16.1, U1.2 (OUT), U4.2 (OUT), U7.2 (OUT), U10.2 (OUT), U13.2 (OUT), U16.2 (OUT), U19.2 (OUT), U22.2 (OUT)
HallOut2: J16.2, U2.2 (OUT), U5.2 (OUT), U8.2 (OUT), U11.2 (OUT), U14.2 (OUT), U17.2 (OUT), U20.2 (OUT), U23.2 (OUT)
HallOut3: J16.3, U3.2 (OUT), U6.2 (OUT), U9.2 (OUT), U12.2 (OUT), U15.2 (OUT), U18.2 (OUT), U21.2 (OUT), U24.2 (OUT)
LedIn: D24.2 (DIN), J18.2
LedIn_side_a: J1.2, J13.2
LedOut: D3.4 (DOUT), J7.2
unnamed: D1.2 (DIN), D4.4 (DOUT)
unnamed: D1.4 (DOUT), D2.2 (DIN)
unnamed: D2.4 (DOUT), D3.2 (DIN)
unnamed: D4.2 (DIN), D5.4 (DOUT)
unnamed: D5.2 (DIN), D6.4 (DOUT)
unnamed: D6.2 (DIN), D9.4 (DOUT)
unnamed: D7.4 (DOUT), D8.2 (DIN)
unnamed: D8.4 (DOUT), D9.2 (DIN)
unnamed: D10.2 (DIN), D11.4 (DOUT)
unnamed: D7.2 (DIN), D10.4 (DOUT)
unnamed: D11.2 (DIN), D12.4 (DOUT)
unnamed: D12.2 (DIN), D15.4 (DOUT)
unnamed: D13.2 (DIN), D16.4 (DOUT)
unnamed: D13.4 (DOUT), D14.2 (DIN)
unnamed: D14.4 (DOUT), D15.2 (DIN)
unnamed: D16.2 (DIN), D17.4 (DOUT)
unnamed: D17.2 (DIN), D18.4 (DOUT)
unnamed: D18.2 (DIN), D21.4 (DOUT)
unnamed: D19.2 (DIN), D22.4 (DOUT)
unnamed: D19.4 (DOUT), D20.2 (DIN)
unnamed: D20.4 (DOUT), D21.2 (DIN)
unnamed: D22.2 (DIN), D23.4 (DOUT)
unnamed: D23.2 (DIN), D24.4 (DOUT)
unnamed: Q1.1 (B), R1.2
unnamed: Q2.1 (B), R2.2
unnamed: Q3.1 (B), R3.2
unnamed: Q4.1 (B), R4.2
unnamed: Q5.1 (B), R5.2
unnamed: Q6.1 (B), R6.2
unnamed: Q7.1 (B), R7.2
unnamed: Q8.1 (B), R8.2
P: C1.1, C2.1, C3.1, C4.1, C5.1, C6.1, C7.1, C8.1, C9.1, C10.1, C11.1, C12.1, C13.1, C14.1, C15.1, C16.1, C17.1, C18.1, C19.1, C20.1, C21.1, C22.1, C23.1, C24.1, CI1.2, CI2.2, CI3.2, D1.3 (VDD), D2.3 (VDD), D3.3 (VDD), D4.3 (VDD), D5.3 (VDD), D6.3 (VDD), D7.3 (VDD), D8.3 (VDD), D9.3 (VDD), D10.3 (VDD), D11.3 (VDD), D12.3 (VDD), D13.3 (VDD), D14.3 (VDD), D15.3 (VDD), D16.3 (VDD), D17.3 (VDD), D18.3 (VDD), D19.3 (VDD), D20.3 (VDD), D21.3 (VDD), D22.3 (VDD), D23.3 (VDD), D24.3 (VDD), J18.1, UI1.16 (VCC), UI2.3 (VI)
P3.3: CI4.2, CI5.2, Q1.2 (E), Q2.2 (E), Q3.2 (E), Q4.2 (E), Q5.2 (E), Q6.2 (E), Q7.2 (E), Q8.2 (E), UI2.2 (VO)
PQ1: J2.2, J8.1, Q1.3 (C), U1.1 (VCC), U2.1 (VCC), U3.1 (VCC)
PQ2: J2.1, J8.2, Q2.3 (C), U4.1 (VCC), U5.1 (VCC), U6.1 (VCC)
PQ3: J3.2, J9.1, Q3.3 (C), U7.1 (VCC), U8.1 (VCC), U9.1 (VCC)
PQ4: J3.1, J9.2, Q4.3 (C), U10.1 (VCC), U11.1 (VCC), U12.1 (VCC)
PQ5: J5.2, J11.1, Q5.3 (C), U13.1 (VCC), U14.1 (VCC), U15.1 (VCC)
PQ6: J5.1, J11.2, Q6.3 (C), U16.1 (VCC), U17.1 (VCC), U18.1 (VCC)
PQ7: J6.2, J12.1, Q7.3 (C), U19.1 (VCC), U20.1 (VCC), U21.1 (VCC)
PQ8: J6.1, J12.2, Q8.3 (C), U22.1 (VCC), U23.1 (VCC), U24.1 (VCC)
P_side_a: J1.3, J13.3
P_side_b: J7.1, J19.2
Q1: R1.1, UI1.15 (Y0)
Q2: R2.1, UI1.14 (Y1)
Q3: R3.1, UI1.13 (Y2)
Q4: R4.1, UI1.12 (Y3)
Q5: R5.1, UI1.11 (Y4)
Q6: R6.1, UI1.10 (Y5)
Q7: R7.1, UI1.9 (Y6)
Q8: R8.1, UI1.7 (Y7)

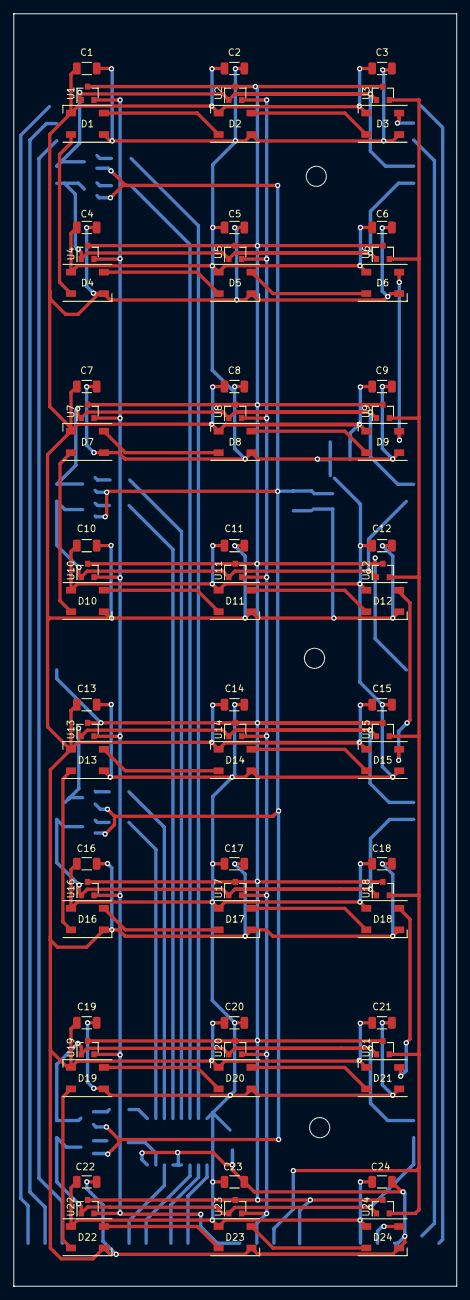
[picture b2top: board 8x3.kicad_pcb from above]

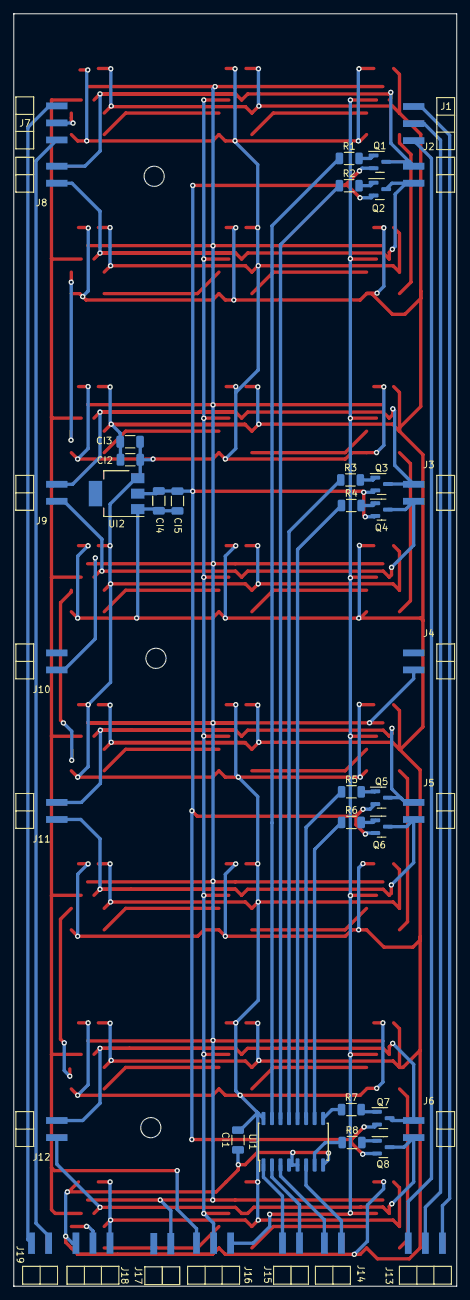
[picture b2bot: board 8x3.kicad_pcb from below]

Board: 2 copper layers, 66.0 x 189.6 mm, 117 parts (42 on the bottom side), 65 nets.

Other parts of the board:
M1, M2, M3: MountingHole_3mm

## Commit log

2023-12-18 Restart history for Saiboard 1.0
2024-03-28 Add connection retry
2024-03-28 #74 #75
